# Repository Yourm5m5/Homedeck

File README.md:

# HomeDeck

**A 7" desk touchscreen for Home Assistant that shows your home at a glance and wakes up when you walk over.**

## What is HomeDeck?

HomeDeck is a 7" smart display that sits on a desk or bench and connects to Home Assistant over Wi-Fi. At a glance it shows the time, weather, calendar, energy use, and whether doors or windows are open. One tap controls lights, fans, air-con, scenes and music.

It's built around a Sunton ESP32-S3 7" touchscreen board, plus a **custom add-on PCB I designed in KiCad**. The add-on board provides protected USB-C power and three sensors:

- **LD2410C mmWave radar** notices when someone is in front of the panel (even sitting still) and wakes the screen
- **BH1750 light sensor** dims the screen automatically in a dark room
- **SHT40** reads room temperature and humidity and reports them back to Home Assistant

A small buzzer gives touch feedback and alerts. Everything sits in a 3D-printed enclosure I modelled in Fusion 360, tilted back 20° so it's easy to read and tap from a chair.

---

## Why I built it

I use Home Assistant at home, but controlling anything means pulling out my phone, unlocking it and opening an app, which is often slower than walking to the light switch. I wanted something that's **always on and always in the same place**: glance to see what's going on, tap once to change it.

You can buy smart displays, but most are locked to one company's ecosystem, rely on the cloud, and can't be customized. HomeDeck runs **locally** through ESPHome and Home Assistant, so it keeps working without the internet and shows exactly what I want.

I also wanted a project that would teach me real hardware skills: drawing a schematic, routing a two-layer PCB, modelling a multi-part enclosure and writing firmware, rather than just plugging modules together.

---

## Features

- 7" 800×480 capacitive touchscreen
- Controls lights, fans, AC, scenes and media through Home Assistant
- Shows time, weather, calendar, energy use and alerts
- Wakes automatically when someone walks up (mmWave presence)
- Auto-brightness from the ambient light sensor
- Reports room temperature and humidity to Home Assistant
- Buzzer for touch feedback, timers and doorbell alerts
- Fully local: ESPHome + LVGL, no cloud needed
- One USB-C cable for power

---

## How it works

The Sunton board's ESP32-S3 drives the display and runs ESPHome with an LVGL interface. The display uses almost every GPIO, so my add-on PCB connects through the few left on the board's expansion headers:

| Signal | Part | ESP32 pin | Header |
|---|---|---|---|
| I2C SDA / SCL | SHT40 + BH1750 | GPIO19 / GPIO20 | P3 (shared with touch, no address conflicts) |
| UART RX / TX | LD2410C | GPIO44 / GPIO43 | P1 |
| Presence output | LD2410C | GPIO17 | P4 |
| Buzzer (via NPN transistor) | Piezo | GPIO18 | P4 |
| 5 V power in | USB-C | n/a | P1 |

---

## Custom PCB

Designed in KiCad: a ~60 × 45 mm two-layer board with power traces on the front, signals on the back, ground fill on both sides and stitching vias. It passes DRC with **0 errors**.

**Power input:** USB-C (5.1 kΩ CC resistors) → 2 A polyfuse → SMAJ5.0CA TVS diode → 10 µF + 100 nF decoupling.

---

## Enclosure

Modelled in Fusion 360 as four 3D-printed parts:

1. **Front bezel** holds the screen behind a 2 mm lip and has a sensor window at the top
2. **Back shell** has vent slots so the SHT40 reads room air instead of screen heat
3. **Base** (190 × 120 × 24 mm) holds the display at 20°, with space for the PCB inside
4. **Bottom plate** mounts the add-on PCB on standoffs and has rubber feet underneath

> Screen-related sizes are estimates and will be checked against the real Sunton board before the final print.

---

## Bill of materials

All parts from **AliExpress** except the custom PCB, which comes from **JLCPCB**. Prices are **approximate AUD** and change with sales, exchange rates and shipping, so check the listing before ordering. Many small parts only come in packs, so you'll have spares.

### Electronics

| # | Part | Qty | Approx. AUD |
|---|---|---|---|
| 1 | Sunton ESP32-8048S070**C** (7" 800×480, ESP32-S3, capacitive touch) | 1 | $70.00 |
| 2 | HLK-LD2410C 24 GHz mmWave presence sensor | 1 | $6.00 |
| 3 | SHT40 temperature/humidity breakout module | 1 | $4.50 |
| 4 | BH1750 (GY-302) light sensor module | 1 | $3.00 |
| 5 | Passive piezo buzzer 12 mm (pack of 10) | 1 pack | $3.00 |
| 6 | MMBT3904 NPN transistor, SOT-23 (pack of 100) | 1 pack | $2.50 |
| 7 | USB-C 6-pin power-only socket (pack of 10) | 1 pack | $3.00 |
| 8 | 2 A polyfuse, 1812 (pack of 20) | 1 pack | $3.00 |
| 9 | SMAJ5.0CA TVS diode (pack of 50) | 1 pack | $3.00 |
| 10 | 0805 resistor + capacitor sample kit | 1 kit | $8.00 |
| 11 | 1.25 mm 4-pin connectors + pre-crimped cables | 1 set | $5.00 |
| 12 | 2.54 mm female header strips | 1 pack | $2.50 |
| 13 | Custom PCB, 5 pcs + shipping (**JLCPCB**) | 1 order | $18.00 |
| | **Electronics subtotal** | | **$131.50** |

### Enclosure

| # | Part | Qty | Approx. AUD |
|---|---|---|---|
| 14 | PETG filament (~300 g of a 1 kg roll) | 1 | $8.00 |
| 15 | M3 brass heat-set inserts (pack of 50) | 1 pack | $7.00 |
| 16 | M3 screw assortment (M3×6, M3×16) | 1 kit | $8.00 |
| 17 | Self-adhesive rubber feet | 1 pack | $3.00 |
| | **Enclosure subtotal** | | **$26.00** |

### Power

| # | Part | Qty | Approx. AUD |
|---|---|---|---|
| 18 | USB-C power supply, 5 V / 3 A | 1 | $10.00 |
| 19 | USB-C cable, 1 m | 1 | $4.00 |
| | **Power subtotal** | | **$14.00** |

### Total

| | AUD |
|---|---|
| Electronics | $131.50 |
| Enclosure | $26.00 |
| Power | $14.00 |
| **Estimated total** | **≈ $171.50** |

---

## Changes after review

The first review asked for better firmware documentation and an exploded view. What changed:

Firmware: commented every section of homedeck.yaml and wrote FIRMWARE.md, explaining each sensor (what it does, how it's read, how it's used) and how every LVGL element is wired to Home Assistant, with code snippets and diagrams
Exploded view: built a full assembly in Fusion 360 with every component and screw, plus ASSEMBLY.md
Design fix found along the way: the exploded view showed the radar and light sensor had nowhere to mount, so I added a sensor bay behind the top bezel (bezel 116 → 128 mm) and an SHT40 cradle with its own vents in the back shell

---

## Acknowledgements

- Sunton pinout info from [ESP3D](https://esp3d.io/esp3d-tft/version_1x/hardware/esp32-s3/sunton-70-8048/) and [Blakadder's templates](https://templates.blakadder.com/sunton_ESP32-8048S070.html)
- Built with [KiCad](https://www.kicad.org/), [Fusion 360](https://www.autodesk.com/products/fusion-360), [ESPHome](https://esphome.io/) and [Home Assistant](https://www.home-assistant.io/)
- AI assistance (Claude) was used for planning, guidance, diagrams and a reference enclosure model

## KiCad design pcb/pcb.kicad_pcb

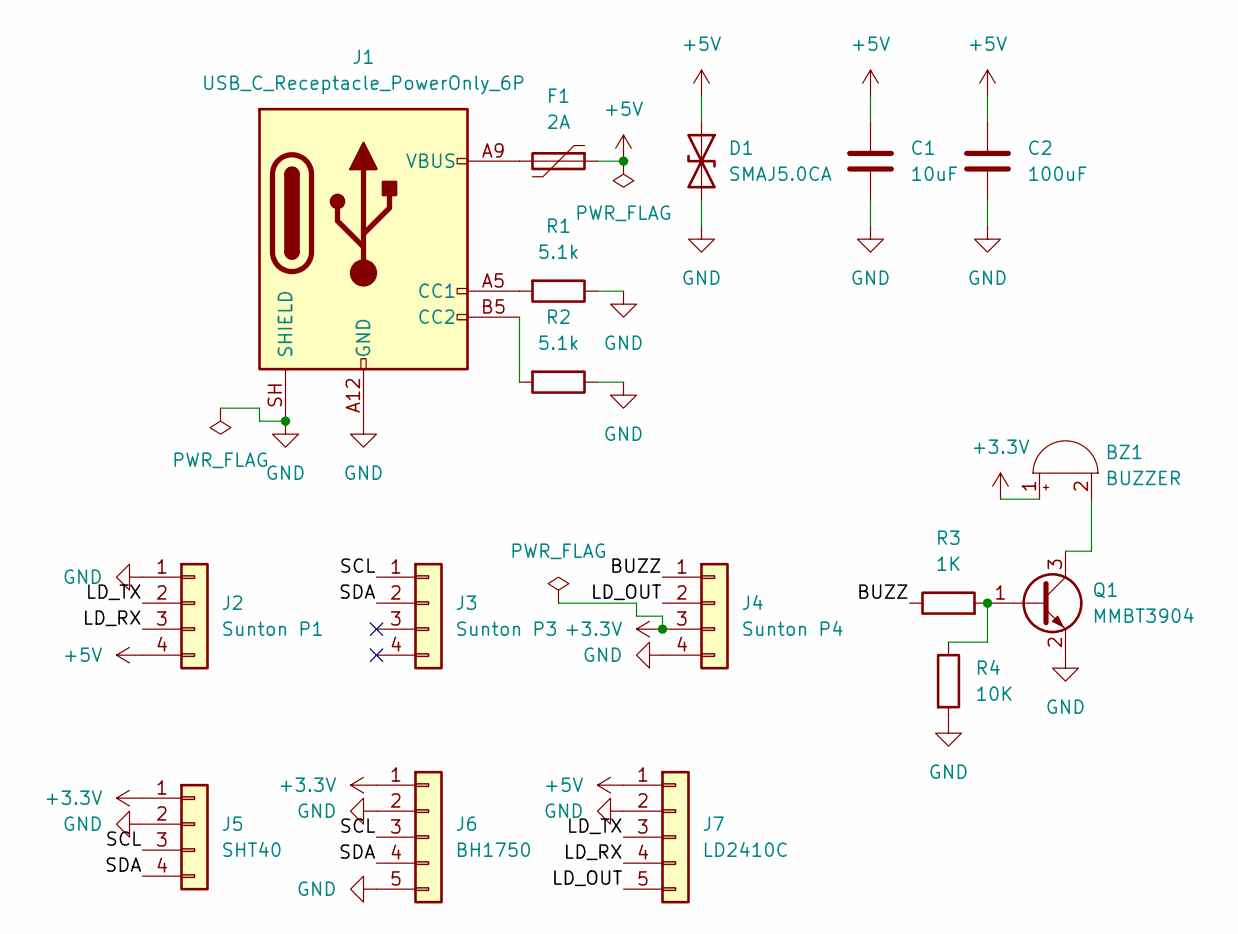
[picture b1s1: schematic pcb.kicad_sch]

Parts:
BZ1: BUZZER; Buzzer_12x9.5RM7.6
C1: 10uF; C_0805_2012Metric
C2: 100uF; C_0805_2012Metric
D1: SMAJ5.0CA; D_SMA
F1: 2A; Fuse_1812_4532Metric
J1: USB_C_Receptacle_PowerOnly_6P; USB_C_Receptacle_GCT_USB4125-xx-x-0190_6P_TopMnt_Horizontal
J2: Sunton P1; Molex_PicoBlade_53047-0410_1x04_P1.25mm_Vertical
J3: Sunton P3; Molex_PicoBlade_53047-0410_1x04_P1.25mm_Vertical
J4: Sunton P4; Molex_PicoBlade_53047-0410_1x04_P1.25mm_Vertical
J5: SHT40; PinSocket_1x04_P2.54mm_Vertical
J6: BH1750; PinSocket_1x05_P2.54mm_Vertical
J7: LD2410C; PinSocket_1x05_P2.54mm_Vertical
Q1: MMBT3904; SOT-23
R1, R2: 5.1k; R_0805_2012Metric
R3: 1K; R_0805_2012Metric
R4: 10K; R_0805_2012Metric

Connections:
+3.3V: BZ1.1 (+), J4.3, J5.1, J6.1
+5V: C1.1, C2.1, D1.1 (A1), F1.1, J2.4, J7.1
/BUZZ: J4.1, R3.1
/LD_OUT: J4.2, J7.5
/LD_RX: J2.3, J7.4
/LD_TX: J2.2, J7.3
/SCL: J3.1, J5.3, J6.3
/SDA: J3.2, J5.4, J6.4
GND: C1.2, C2.2, D1.2 (A2), J1.A12 (GND), J1.B12 (GND), J1.SH (SHIELD), J2.1, J4.4, J5.2, J6.2, J6.5, J7.2, Q1.2 (E), R1.1, R2.1, R4.2
unnamed: BZ1.2 (-), Q1.3 (C)
unnamed: F1.2, J1.A9 (VBUS), J1.B9 (VBUS)
unnamed: J1.A5 (CC1), R1.2
unnamed: J1.B5 (CC2), R2.2
unnamed: Q1.1 (B), R3.2, R4.1

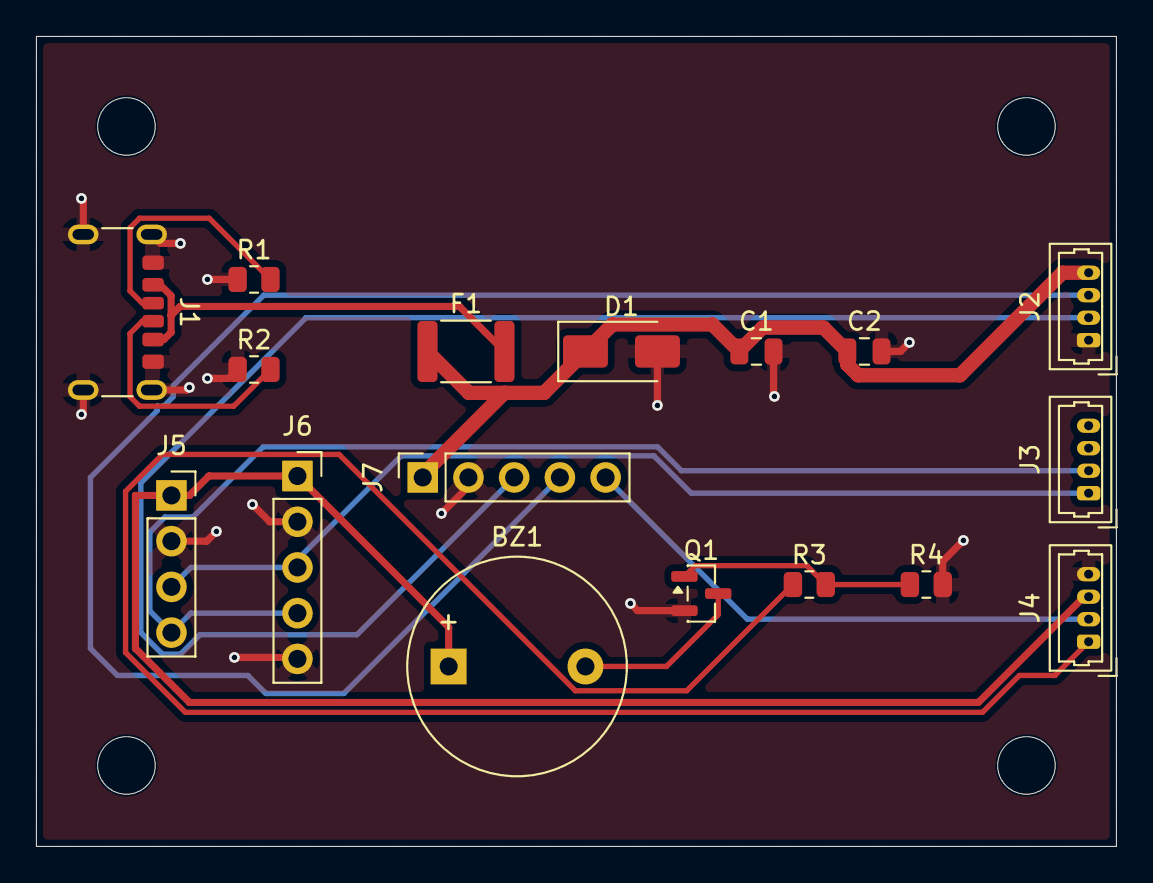
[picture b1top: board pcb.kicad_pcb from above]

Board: 2 copper layers, 60.0 x 45.0 mm, 17 parts (0 on the bottom side), 14 nets.
